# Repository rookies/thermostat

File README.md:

thermostat
==========

Simple thermostat using an Arduino, a DS18B20 sensor and a 433 MHz wireless socket.

## Sources
* [Arduino Projekt: Funksteckdose steuern](https://draeger-it.blog/arduino-projekt-funksteckdose-steuern/) (german)
* [Arduino Tutorial 37: 433 MHz Sender & Empfänger](https://draeger-it.blog/arduino-tutorial-433mhz-sender-empfaenger/) (german)

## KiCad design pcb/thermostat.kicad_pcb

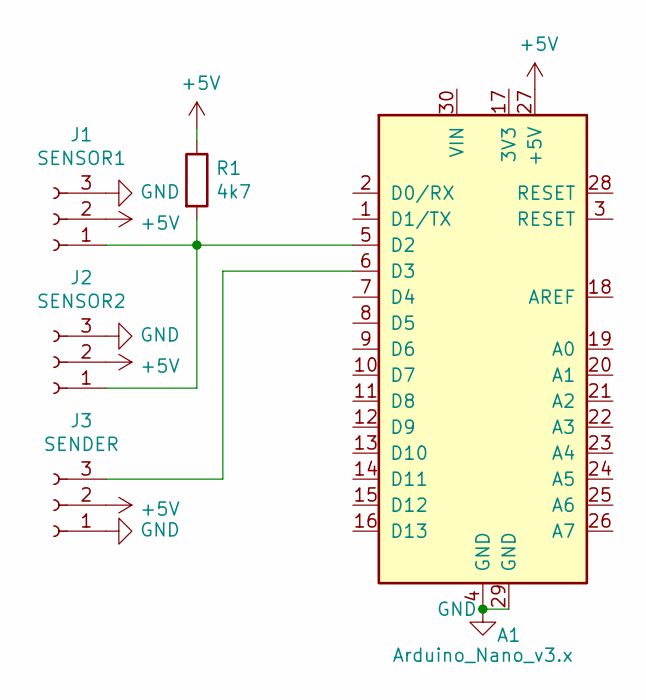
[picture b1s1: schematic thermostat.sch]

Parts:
A1: Arduino_Nano_v3.x; Arduino_Nano
J1: SENSOR1; PinSocket_1x03_P2.54mm_Vertical
J2: SENSOR2; PinSocket_1x03_P2.54mm_Vertical
J3: SENDER; PinSocket_1x03_P2.54mm_Vertical
R1: 4k7; R_0805_2012Metric

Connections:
+5V: A1.27 (+5V), J1.2, J2.2, J3.2, R1.1
GND: A1.4 (GND), A1.29 (GND), J1.3, J2.3, J3.1
unnamed: A1.5 (D2), J1.1, J2.1, R1.2
unnamed: A1.6 (D3), J3.3

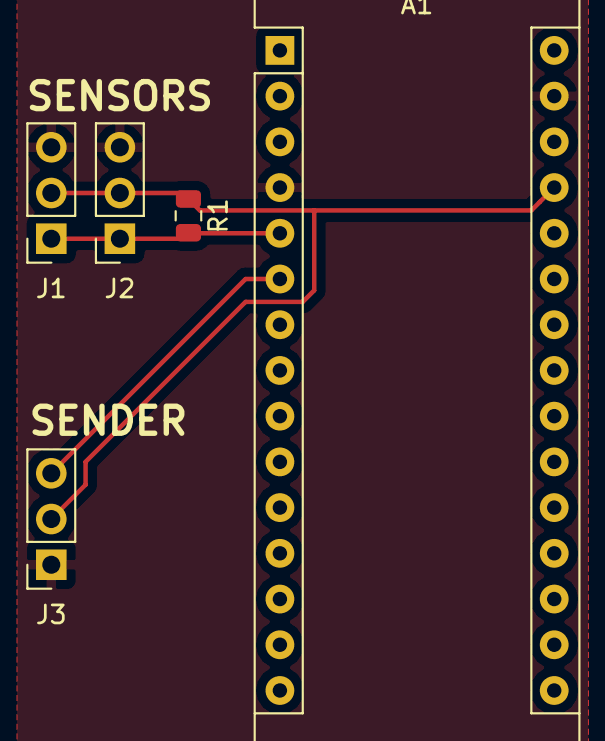
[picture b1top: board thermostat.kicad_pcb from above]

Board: 2 copper layers, 5 parts (0 on the bottom side), 4 nets.

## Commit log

2019-02-24 init
2019-03-03 support for live plot updates
2019-03-03 runtime-adjustable temperature bounds via serial
2019-03-03 use argparse for plot.py
2019-03-03 more experiments
2019-03-05 better config documentation
2019-03-31 adapted config to final board layout
2019-03-31 toggle builtin LED
2020-10-05 improve serial communication
2020-10-05 add simple GUI
2020-10-05 send proper status messages if disabled
2020-10-05 GUI: improve status text
2022-01-30 Switch off heater when disabled
